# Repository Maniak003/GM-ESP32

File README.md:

<!DOCTYPE html>
<html lang="en" data-color-mode="auto" data-light-theme="light" data-dark-theme="dark">
  <head>
    <meta charset="utf-8">
  </head>
    <body class="logged-in env-production page-responsive page-blob" style="word-wrap: break-word;">
      <p> GM counter on ESP32. </p>
      
    </body>
</html>

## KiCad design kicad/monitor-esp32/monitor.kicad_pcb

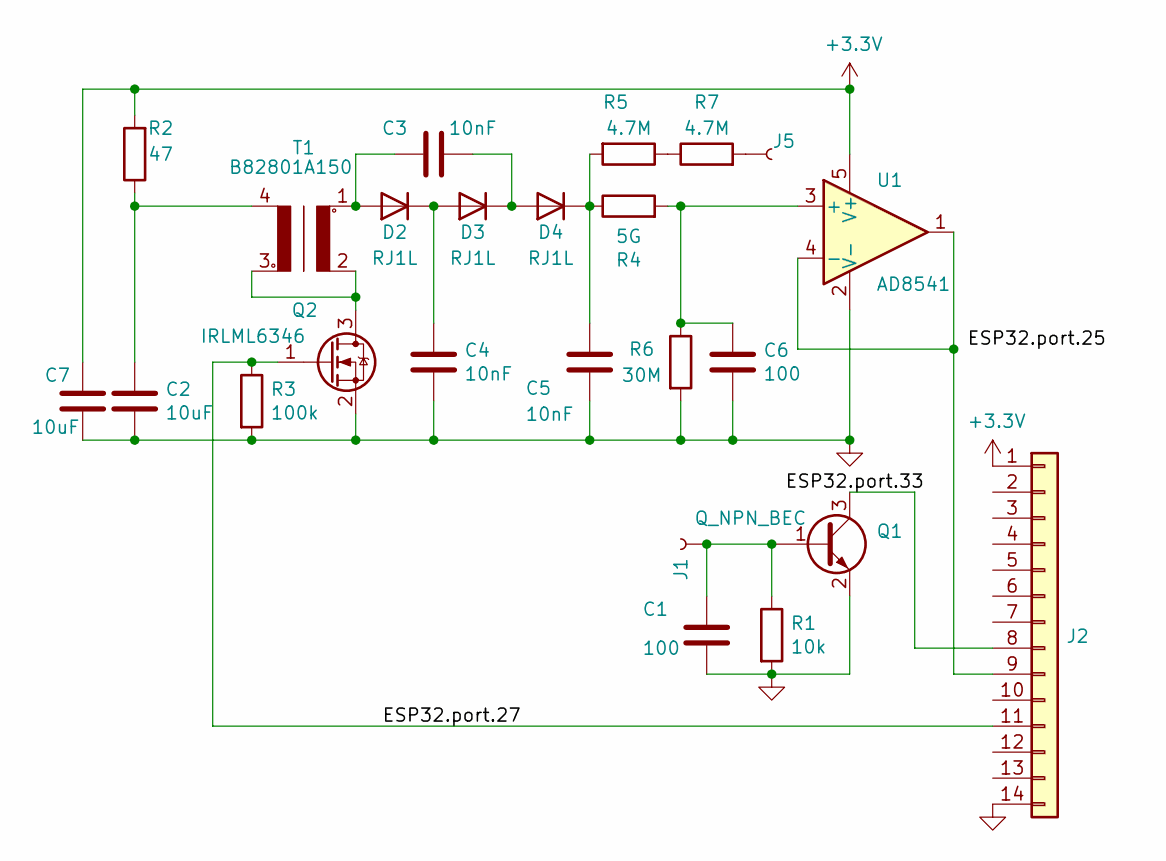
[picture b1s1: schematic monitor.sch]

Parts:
C1, C6: 100; C_0805_2012Metric
C2, C7: 10uF; C_0805_2012Metric
C3, C4, C5: 10nF; C_1812_4532Metric
D2, D3, D4: RJ1L; D_SOD-123
J1, J5: Conn; SMD-CONN
J2: Conn_01x14; PinHeader_1x14_P2.54mm_Horizontal
Q1: Q_NPN_BEC; SOT-23
Q2: IRLML6346; SOT-23
R1: 10k; R_0805_2012Metric
R2: 47; R_0805_2012Metric
R3: 100k; R_0805_2012Metric
R4: 5G; R_2512_6332Metric
R5, R7: 4.7M; R_0805_2012Metric
R6: 30M; R_0805_2012Metric
T1: B82801A150; B82801A1
U1: AD8541; TSOT-23-5

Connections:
+3V3: C7.1, J2.1, R2.2, U1.5 (V+)
/ESP32.port.27: J2.11, Q2.1 (G), R3.1
GND: C1.2, C2.2, C4.2, C5.2, C6.2, C7.2, J2.14, Q1.2 (E), Q2.2 (S), R1.2, R3.2, R6.2, U1.2 (V-)
unnamed: C1.1, J1.1, Q1.1 (B), R1.1
unnamed: C2.1, R2.1, T1.4
unnamed: C3.1, D3.1 (K), D4.2 (A)
unnamed: C3.2, D2.2 (A), T1.1
unnamed: C4.1, D2.1 (K), D3.2 (A)
unnamed: C5.1, D4.1 (K), R4.1, R5.2
unnamed: C6.1, R4.2, R6.1, U1.3 (+)
unnamed: J2.8, Q1.3 (C)
unnamed: J2.9, U1.1, U1.4 (-)
unnamed: J5.1, R7.2
unnamed: Q2.3 (D), T1.2, T1.3
unnamed: R5.1, R7.1

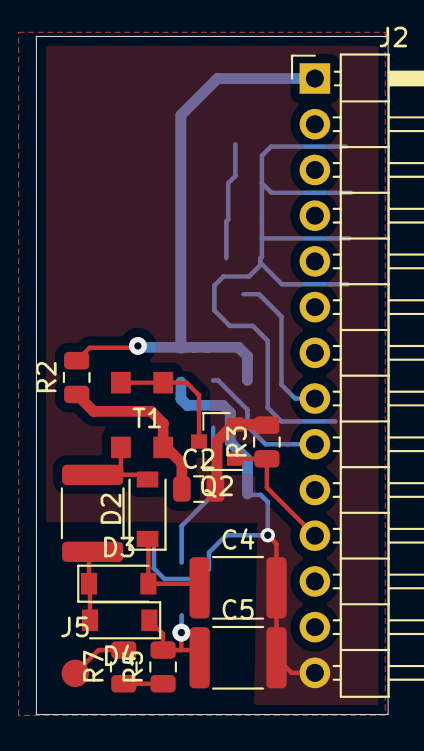
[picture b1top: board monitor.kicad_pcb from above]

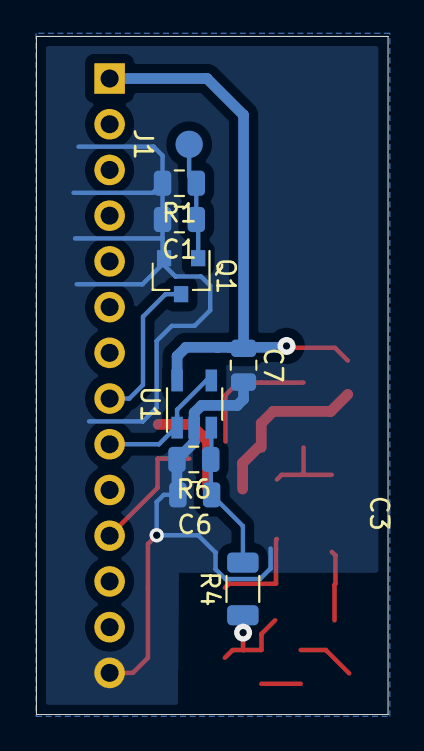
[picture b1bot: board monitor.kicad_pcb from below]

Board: 2 copper layers, 19.5 x 37.7 mm, 24 parts (9 on the bottom side), 15 nets.

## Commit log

2023-06-06 новый файл: kicad/monitor-esp32/fp-info-cache новый файл: kicad/monitor-esp32/monitor-cache.lib новый файл: kicad/monitor-esp32/monitor-rescue.dcm новый файл: kicad/monitor-esp32/monitor-rescue.lib н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
2023-06-06 новый файл: Arduino/GM-ESP32/GM-ESP32.ino
2023-06-06 новый файл: Documents/IMG_20211220_203938.jpg изменено: README.md
2023-06-06 изменено: kicad/monitor-esp32/monitor-cache.lib изменено: kicad/monitor-esp32/monitor.kicad_pcb изменено: kicad/monitor-esp32/monitor.kicad_pcb-bak изменено: kicad/monitor-esp32/monitor.sch изменено: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
2023-06-06 новый файл: Documents/Kamaya_RHC.pdf новый файл: Documents/NG_DS_1773268_A-721582.pdf новый файл: Documents/Ohmite.pdf
2023-06-06 изменено: kicad/monitor-esp32/monitor.sch изменено: kicad/monitor-esp32/monitor.sch-bak
